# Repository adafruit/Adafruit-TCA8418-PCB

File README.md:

## Adafruit TCA8418 Keypad Matrix and GPIO Expander Breakout - STEMMA QT / Qwiic PCB

<a href="http://www.adafruit.com/products/4918"><br/>
Click here to purchase one from the Adafruit shop</a>

PCB files for the Adafruit TCA8418 Keypad Matrix and GPIO Expander Breakout - STEMMA QT / Qwiic. 

Format is EagleCAD schematic and board layout
* https://www.adafruit.com/product/4918

### Description

It's a GPIO expander, it's a keypad matrix driver... its the Adafruit TCA8418 Keypad Matrix and GPIO Expander Breakout - a cute and powerful I2C GPIO expander and keypad matrix driver! This chip is quite fancy, with the ability to act as your I2C multi-tool for handling keypads, buttons or LEDs.

This chip has 18 total 'I/O' pins, 10 columns and 8 rows. You can of course arrange them as a matrix of buttons for a total of 80 switches. Or you can use any subset as individual GPIO input or outputs. The nicest part of the keypad driver is that it has a 10-element event queue, so even if you don't get to the interrupt immediately, keypress and release events will be held for you. Since it's I2C its very easy to use with any microcontroller or computer.

GPIO expanders work like this: you have a board with some number of GPIO but not enough for your project - maybe you need more buttons or LEDs. You could upgrade to a board with massive number of GPIO like the Grand Central, or you could pop on one of these boards. Connect it over I2C and then you can send/receive I2C commands to control the GPIO pins to write and read them. It's going to be slower than direct GPIO access, but maybe that doesn't matter if it takes a millisecond instead of a microsecond. You only need the two I2C pins, and you can even share the I2C port with other sensors and devices. Heck, you can even add more expanders for massive I/O control!

For GPIO expansion, any of the 18 pins can be used as input or output. For inputs, you can also set an optional pull-up and an interrupt output on the INT pin for rising or falling signals. There's also a debouncer that can add a little low-pass filtering for noisy tactile switches. For outputs, you can set them high or low, great for basic LED driving.

For Keypad Matrix driving, theres up to 10 columns and 8 rows. You cannot change a row into a column or vice versa. Pull-ups and matrix scanning is handled for you, with key presses and releases recorded into a 10-element FIFO queue. You can of course set up interrupt output on key press or release so you don't have to poll over and over again. 

We've written both Arduino and CircuitPython/Python libraries for the TCA8418, so you can get started whether you have an Arduino-compatible UNO or a Raspberry Pi 4 - or anything in between. There's also a Linux Kernel driver module if you want to have this natively supported by a single-board-computer.

To get you going fast, we spun up a custom-made PCB in the STEMMA QT form factor, making it easy to interface with. There's a built in 3.3V regulator and level shifting on the I2C lines so you can use this with 3V or 5V microcontrollers.

The STEMMA QT connectors on either side are compatible with the SparkFun Qwiic I2C connectors. This allows you to make solderless connections between your development board and the TCA8418 or to chain it with a wide range of other sensors and accessories using a compatible cable. QT Cable is not included, but we have a variety in the shop. 

### License

Adafruit invests time and resources providing this open source design, please support Adafruit and open-source hardware by purchasing products from [Adafruit](https://www.adafruit.com)!

Designed by Limor Fried/Ladyada for Adafruit Industries.

Creative Commons Attribution/Share-Alike, all text above must be included in any redistribution. 
See license.txt for additional details.

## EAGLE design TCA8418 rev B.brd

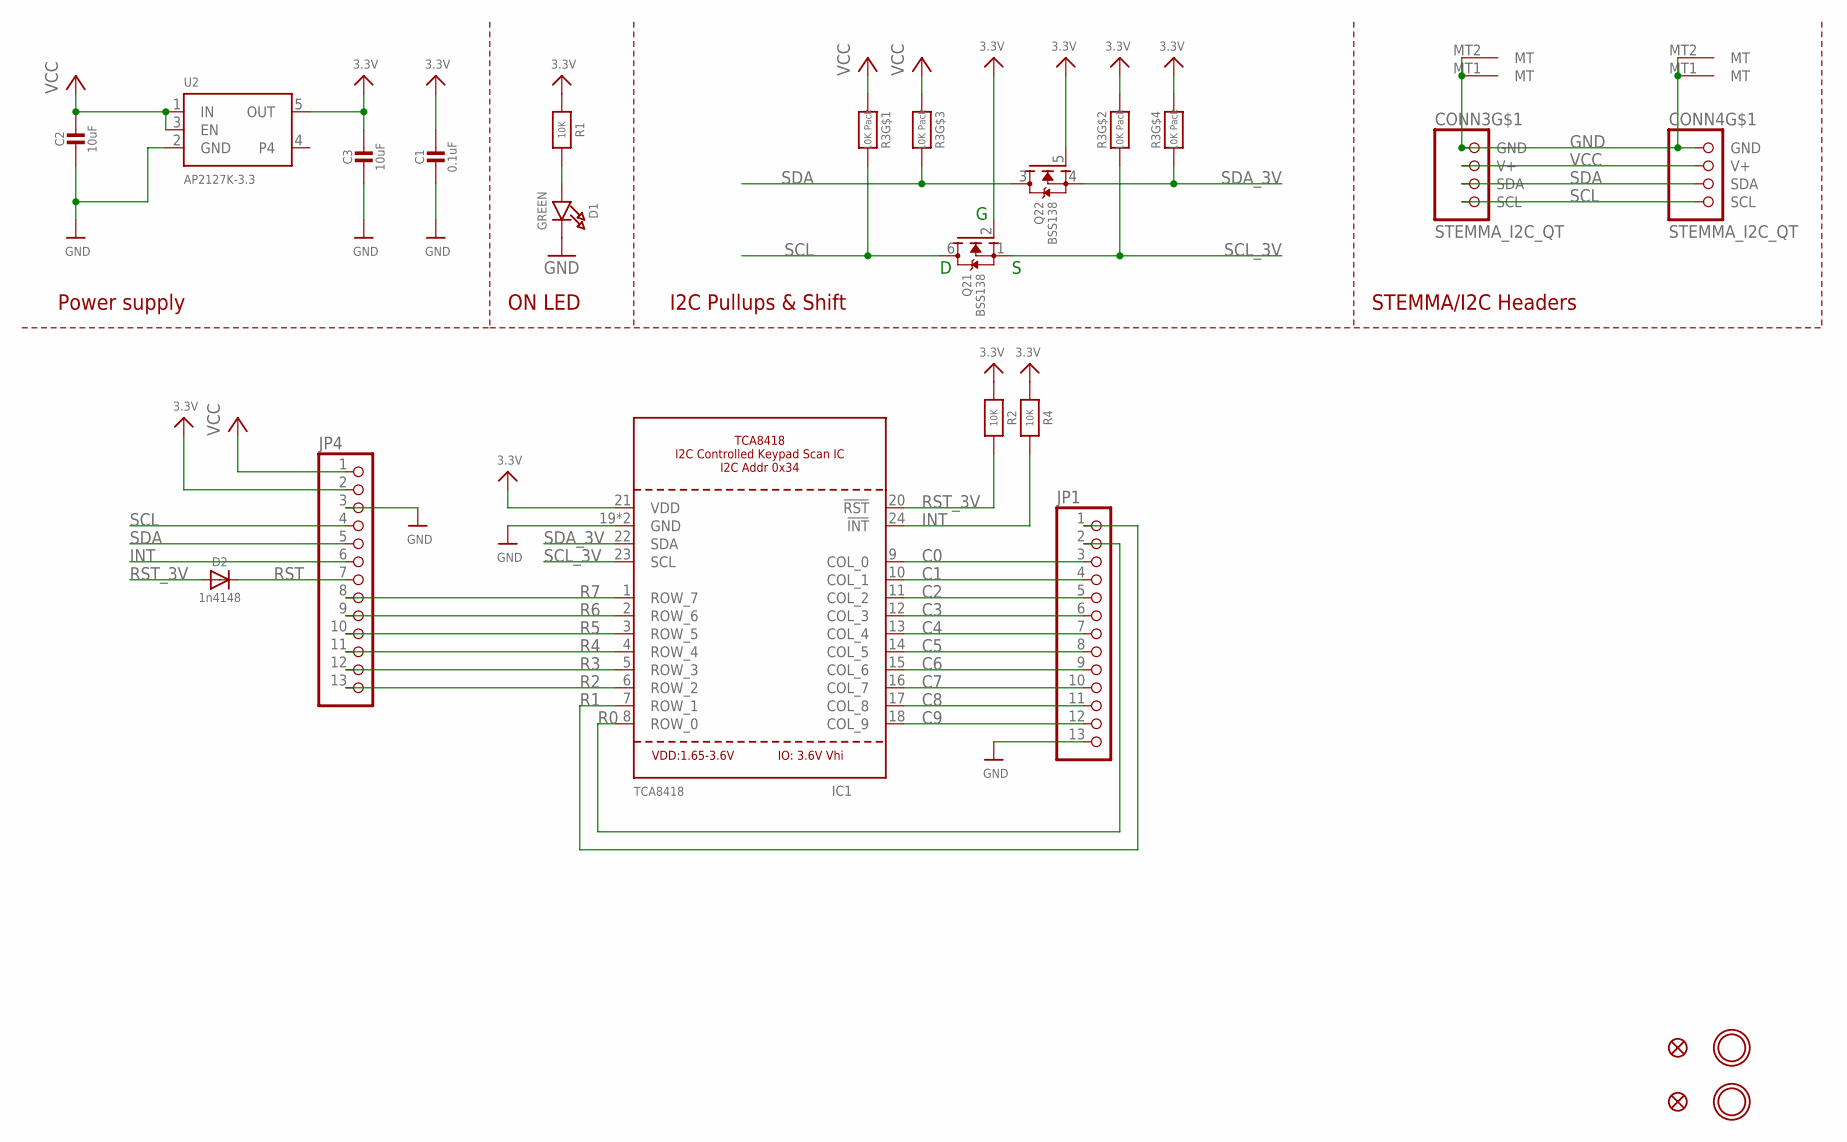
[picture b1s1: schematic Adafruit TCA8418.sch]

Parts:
C1: 0.1uF; 0603-NO
C2, C3: 10uF; 0805-NO
CONN3, CONN4: STEMMA_I2C_QT; JST_SH4
D1: GREEN; CHIPLED_0603_NOOUTLINE
D2: 1n4148; SOD-323
FID3, FID4: FIDUCIAL_1MM
IC1: TCA8418; QFN24_4MM_SMSC
JP1, JP4: HEADER-1X13; 1X13_ROUND_70
Q2: BSS138; SOT363
R1, R2, R4: 10K; 0603-NO
R3: 10K Pack; RESPACK_4X0603
U2: AP2127K-3.3; SOT23-5
U$1, U$17: MOUNTINGHOLE2.5; MOUNTINGHOLE_2.5_PLATED

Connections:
3.3V: C1.1, C3.1, IC1.21 (VDD), JP4.2, Q2.2 (G), Q2.5 (G), R1.1, R2.1, R3.2 (1), R3.4 (1), R4.1, U2.5 (OUT)
C0: IC1.9 (COL_0), JP1.3
C1: IC1.10 (COL_1), JP1.4
C2: IC1.11 (COL_2), JP1.5
C3: IC1.12 (COL_3), JP1.6
C4: IC1.13 (COL_4), JP1.7
C5: IC1.14 (COL_5), JP1.8
C6: IC1.15 (COL_6), JP1.9
C7: IC1.16 (COL_7), JP1.10
C8: IC1.17 (COL_8), JP1.11
C9: IC1.18 (COL_9), JP1.12
GND: C1.2, C2.2, C3.2, CONN3.1 (GND), CONN3.MT1 (MT), CONN3.MT2 (MT), CONN4.1 (GND), CONN4.MT1 (MT), CONN4.MT2 (MT), D1.C, IC1.19 (GND), IC1.THERM (GND), JP1.13, JP4.3, U2.2 (GND)
INT: IC1.24 (!INT), JP4.6, R4.2
unnamed: D1.A, R1.2
R0: IC1.8 (ROW_0), JP1.2
R1: IC1.7 (ROW_1), JP1.1
R2: IC1.6 (ROW_2), JP4.13
R3: IC1.5 (ROW_3), JP4.12
R4: IC1.4 (ROW_4), JP4.11
R5: IC1.3 (ROW_5), JP4.10
R6: IC1.2 (ROW_6), JP4.9
R7: IC1.1 (ROW_7), JP4.8
RST: D2.C, JP4.7
RST_3V: D2.A, IC1.20 (!RST), R2.2
SCL: CONN3.4 (SCL), CONN4.4 (SCL), JP4.4, Q2.6 (D), R3.8 (2)
SCL_3V: IC1.23 (SCL), Q2.1 (S), R3.7 (2)
SDA: CONN3.3 (SDA), CONN4.3 (SDA), JP4.5, Q2.3 (D), R3.6 (2)
SDA_3V: IC1.22 (SDA), Q2.4 (S), R3.5 (2)
VCC: C2.1, CONN3.2 (V+), CONN4.2 (V+), JP4.1, R3.1, R3.3 (1), U2.1 (IN), U2.3 (EN)

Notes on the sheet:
I2C Pullups & Shift
STEMMA/I2C Headers
ON LED
Power supply

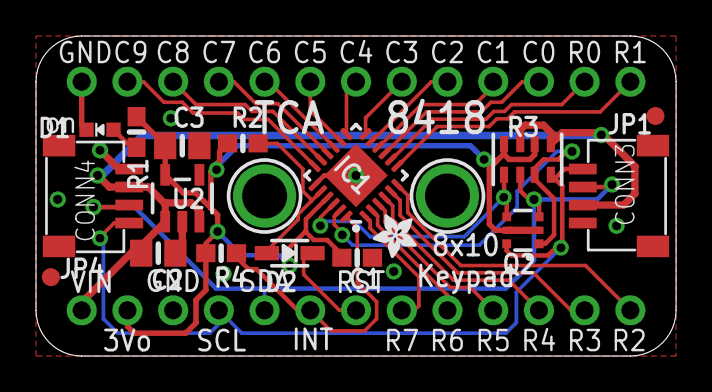
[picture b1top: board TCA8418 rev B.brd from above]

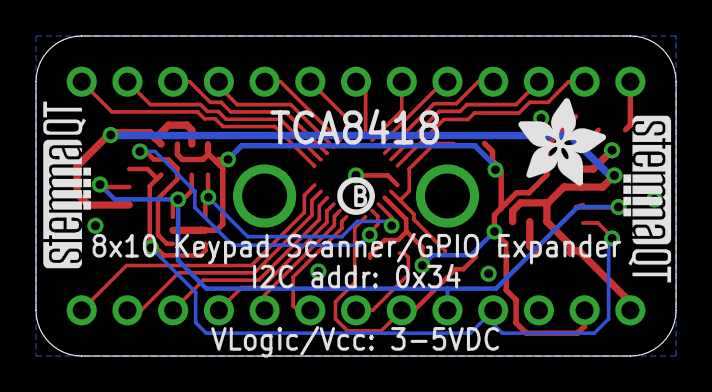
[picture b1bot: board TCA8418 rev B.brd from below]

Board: 2 copper layers, 35.6 x 17.8 mm, 25 parts (4 on the bottom side), 29 nets.

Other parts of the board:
U$12: PCBFEAT-REV-040
U$19: ADAFRUIT_5MM
U$20: ADAFRUIT_2.5MM
U$30, U$31: STEMMAQT

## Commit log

2022-09-15 cookiecutter output
2022-09-15 updating board file names

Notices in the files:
parts and their libraries:
microbuilder: This work is placed in the public domain, and may be freely used for commercial and non-commercial work with the following conditions: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
